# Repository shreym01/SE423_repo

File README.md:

# SE423Spring25
Lab assignment repository for SE423 Spring 2025

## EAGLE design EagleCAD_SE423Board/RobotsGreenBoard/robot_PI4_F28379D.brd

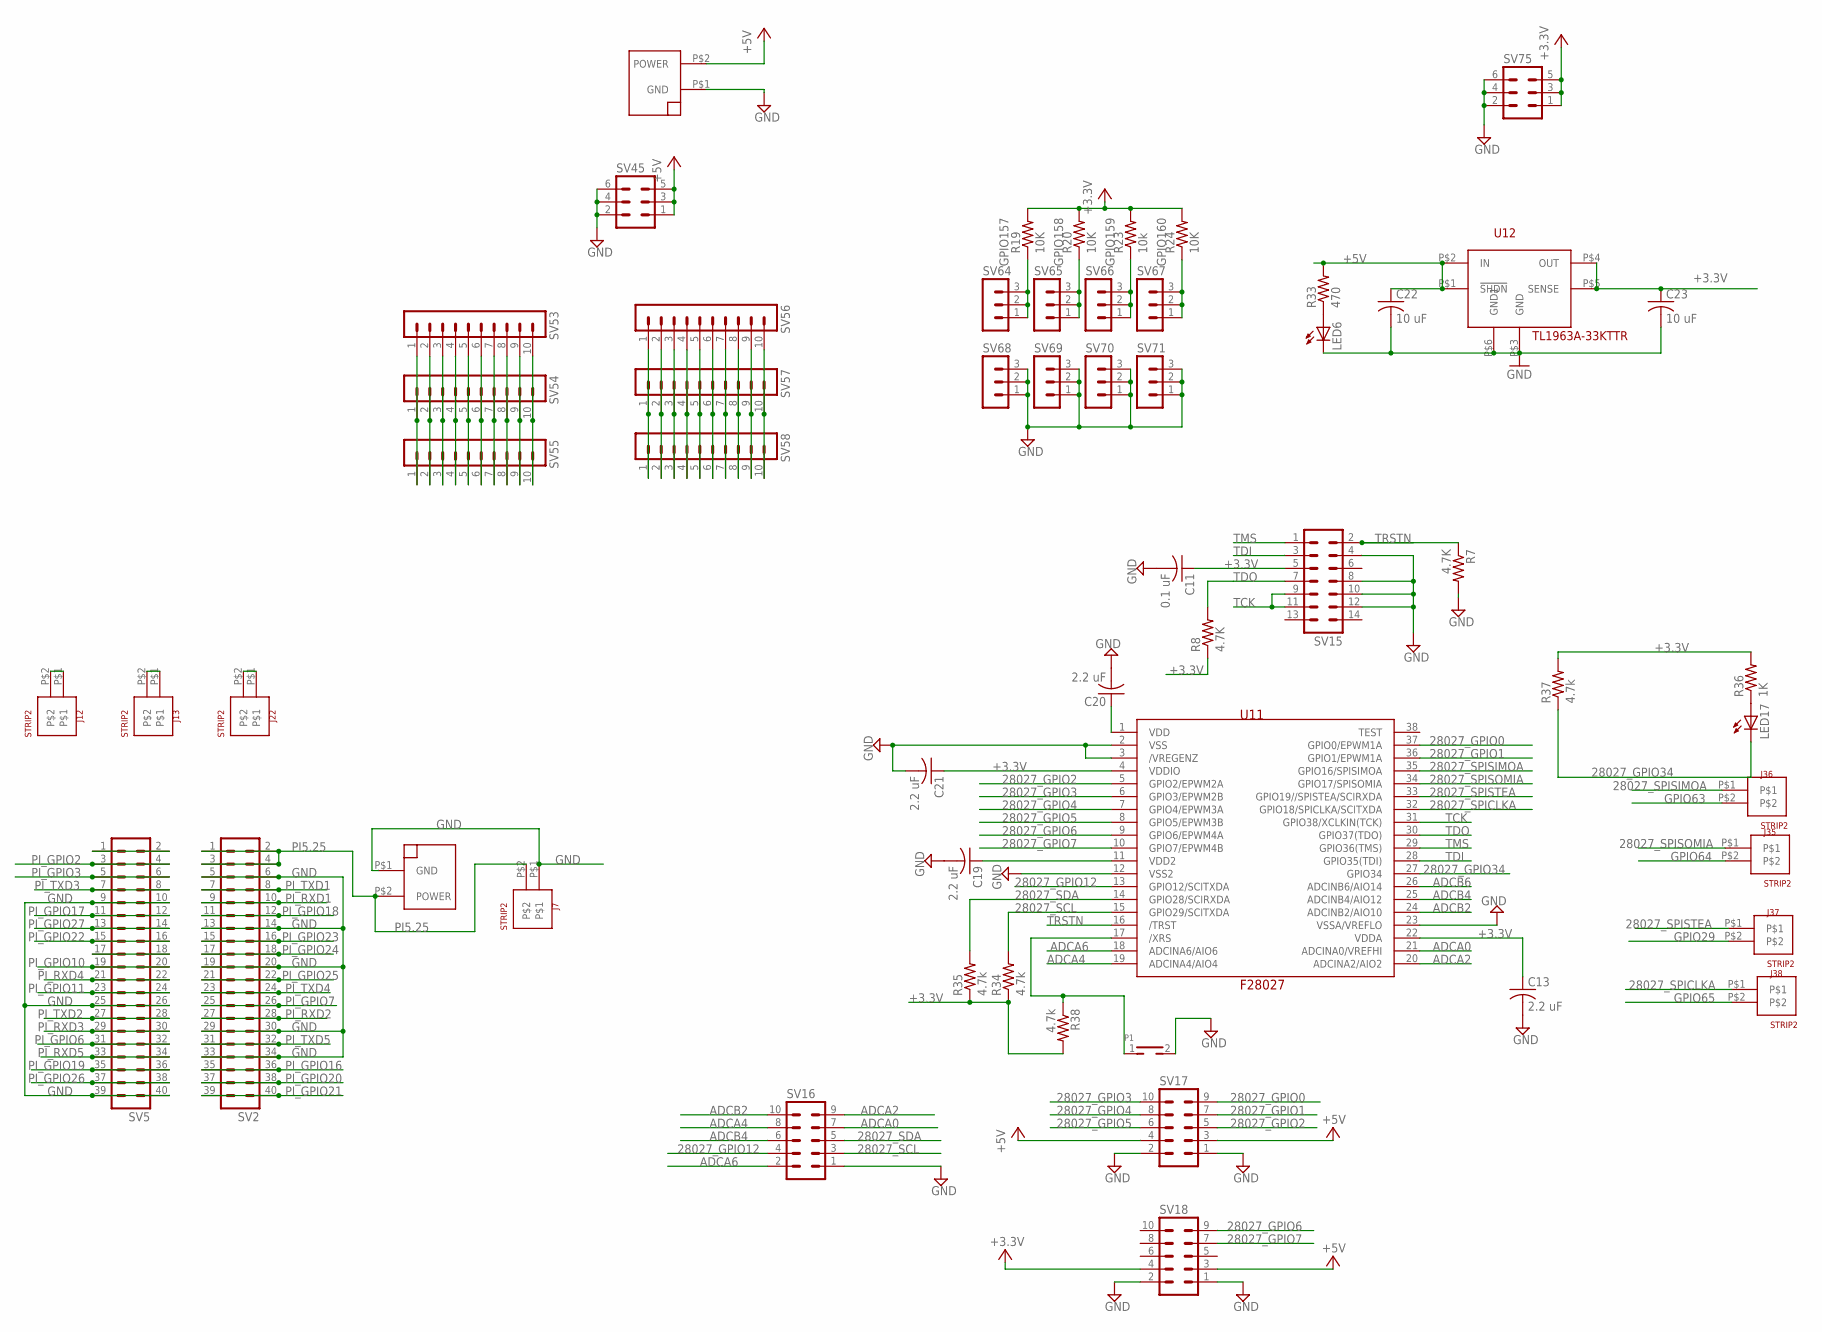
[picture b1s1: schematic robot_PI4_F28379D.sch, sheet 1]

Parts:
C11: 0.1 uF; C1206
C13, C19, C20, C21: 2.2 uF; C1206
C22, C23: 10 uF; C1206
J7, J12, J13, J22, J35, J36, J37, J38: STRIP2
LED6, LED17: LEDCHIPLED_1206; CHIPLED_1206
P1: TH_PUSHBOTTON; TH_PUSHBUTTON
P2, P3: MOLEX_POWER
R7, R8: 4.7K; M1206
R19, R20, R24: 10K; M1206
R23: 10k; M1206
R33: 470; M1206
R34, R35, R37, R38: 4.7k; M1206
R36: 1K; M1206
SV2, SV5: MA20-2
SV15: MA07-2
SV16, SV17, SV18: MA05-2
SV45, SV75: MA03-2
SV53, SV54, SV55, SV56, SV57, SV58: MA10-1
SV64, SV65, SV66, SV67, SV68, SV69, SV70, SV71: MA03-1
U11: F28027; DA38
U12: TL1963A-33KTTR; TL1963AKTTR

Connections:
28027_GPIO0: SV17.9, U11.37 (GPIO0/EPWM1A)
28027_GPIO1: SV17.7, U11.36 (GPIO1/EPWM1A)
28027_GPIO2: SV17.5, U11.5 (GPIO2/EPWM2A)
28027_GPIO3: SV17.10, U11.6 (GPIO3/EPWM2B)
28027_GPIO4: SV17.8, U11.7 (GPIO4/EPWM3A)
28027_GPIO5: SV17.6, U11.8 (GPIO5/EPWM3B)
28027_GPIO6: SV18.9, U11.9 (GPIO6/EPWM4A)
28027_GPIO7: SV18.7, U11.10 (GPIO7/EPWM4B)
28027_GPIO12: SV16.4, U11.13 (GPIO12/SCITXDA)
28027_GPIO34: LED17.C, R37.1, U11.27 (GPIO34)
28027_SCL: R34.2, SV16.3, U11.15 (GPIO29/SCITXDA)
28027_SDA: R35.2, SV16.5, U11.14 (GPIO28/SCIRXDA)
28027_SPICLKA: J38.P$1, U11.32 (GPIO18/SPICLKA/SCITXDA)
28027_SPISIMOA: J36.P$1, U11.35 (GPIO16/SPISIMOA)
28027_SPISOMIA: J35.P$1, U11.34 (GPIO17/SPISOMIA)
28027_SPISTEA: J37.P$1, U11.33 (GPIO19//SPISTEA/SCIRXDA)
+3.3V: C11.1, C13.1, C21.1, C23.1, R8.1, R19.2, R20.2, R23.2, R24.2, R34.1, R35.1, R36.2, R37.2, R38.2, SV15.5, SV18.4, SV75.1, SV75.3, SV75.5, U11.4 (VDDIO), U11.22 (VDDA), U12.P$4 (OUT), U12.P$5 (SENSE); also elsewhere on the board
+5V: C22.1, P3.P$2 (POWER), R33.2, SV17.3, SV17.4, SV18.3, SV45.1, SV45.3, SV45.5, U12.P$1 (!SHDN), U12.P$2 (IN); also elsewhere on the board
ADCA0: SV16.7, U11.21 (ADCINA0/VREFHI)
ADCA2: SV16.9, U11.20 (ADCINA2/AIO2)
ADCA4: SV16.8, U11.19 (ADCINA4/AIO4)
ADCA6: SV16.2, U11.18 (ADCINA6/AIO6)
ADCB2: SV16.10, U11.24 (ADCINB2/AIO10)
ADCB4: SV16.6, U11.25 (ADCINB4/AIO12)
ADCB6: U11.26 (ADCINB6/AIO14)
GND: C11.2, C13.2, C19.2, C20.2, C21.2, C22.2, C23.2, J7.P$1, LED6.C, P1.2, P2.P$1 (GND), P3.P$1 (GND), R7.2, SV2.5, SV2.6, SV2.13, SV2.14, SV2.19, SV2.20, SV2.29, SV2.30, SV2.33, SV2.34, SV5.9, SV5.10, SV5.25, SV5.26, SV5.39, SV5.40, SV15.4, SV15.8, SV15.10, SV15.12, SV16.1, SV17.1, SV17.2, SV18.1, SV18.2, SV45.2, SV45.4, SV45.6, SV68.1, SV68.2, SV68.3, SV69.1, SV69.2, SV69.3, SV70.1, SV70.2, SV70.3, SV71.1, SV71.2, SV71.3, SV75.2, SV75.4, SV75.6, U11.2 (VSS), U11.3 (/VREGENZ), U11.12 (VSS2), U11.23 (VSSA/VREFLO), U12.P$3 (GND), U12.P$6 (GND1); also elsewhere on the board
GPIO29: J37.P$2; also elsewhere on the board
GPIO63: J36.P$2; also elsewhere on the board
GPIO64: J35.P$2; also elsewhere on the board
GPIO65: J38.P$2; also elsewhere on the board
GPIO157: R19.1, SV64.1, SV64.2, SV64.3; also elsewhere on the board
GPIO158: R20.1, SV65.1, SV65.2, SV65.3; also elsewhere on the board
GPIO159: R23.1, SV66.1, SV66.2, SV66.3; also elsewhere on the board
GPIO160: R24.1, SV67.1, SV67.2, SV67.3; also elsewhere on the board
unnamed: SV5.1, SV5.2
unnamed: SV5.17, SV5.18
unnamed: LED6.A, R33.1
unnamed: J12.P$1, J12.P$2
unnamed: J13.P$1, J13.P$2
unnamed: J22.P$1, J22.P$2
unnamed: SV53.1, SV54.1, SV55.1
unnamed: SV53.2, SV54.2, SV55.2
unnamed: SV53.3, SV54.3, SV55.3
unnamed: SV53.4, SV54.4, SV55.4
unnamed: SV53.5, SV54.5, SV55.5
unnamed: SV53.6, SV54.6, SV55.6
unnamed: SV53.7, SV54.7, SV55.7
unnamed: SV53.8, SV54.8, SV55.8
unnamed: SV53.9, SV54.9, SV55.9
unnamed: SV53.10, SV54.10, SV55.10
unnamed: SV56.1, SV57.1, SV58.1
unnamed: SV56.2, SV57.2, SV58.2
unnamed: SV56.3, SV57.3, SV58.3
unnamed: SV56.4, SV57.4, SV58.4
unnamed: SV56.5, SV57.5, SV58.5
unnamed: SV56.6, SV57.6, SV58.6
unnamed: SV56.7, SV57.7, SV58.7
unnamed: SV56.8, SV57.8, SV58.8
unnamed: SV56.9, SV57.9, SV58.9
unnamed: SV56.10, SV57.10, SV58.10
unnamed: C20.1, U11.1 (VDD)
unnamed: C19.1, U11.11 (VDD2)
unnamed: P1.1, R38.1, U11.17 (/XRS)
unnamed: LED17.A, R36.1
PI5.25: J7.P$2, P2.P$2 (POWER), SV2.1, SV2.2, SV2.3, SV2.4
PI_GPIO2: SV5.3, SV5.4; also elsewhere on the board
PI_GPIO3: SV5.5, SV5.6; also elsewhere on the board
PI_GPIO6: SV5.31, SV5.32; also elsewhere on the board
PI_GPIO7: SV2.25, SV2.26; also elsewhere on the board
PI_GPIO10: SV5.19, SV5.20; also elsewhere on the board
PI_GPIO11: SV5.23, SV5.24; also elsewhere on the board
PI_GPIO16: SV2.35, SV2.36
PI_GPIO17: SV5.11, SV5.12
PI_GPIO18: SV2.11, SV2.12
PI_GPIO19: SV5.35, SV5.36
PI_GPIO20: SV2.37, SV2.38
PI_GPIO21: SV2.39, SV2.40
PI_GPIO22: SV5.15, SV5.16
PI_GPIO23: SV2.15, SV2.16
PI_GPIO24: SV2.17, SV2.18
PI_GPIO25: SV2.21, SV2.22
PI_GPIO26: SV5.37, SV5.38
PI_GPIO27: SV5.13, SV5.14
PI_RXD1: SV2.9, SV2.10; also elsewhere on the board
PI_RXD2: SV2.27, SV2.28; also elsewhere on the board
PI_RXD3: SV5.29, SV5.30; also elsewhere on the board
PI_RXD4: SV5.21, SV5.22; also elsewhere on the board
PI_RXD5: SV5.33, SV5.34; also elsewhere on the board
PI_TXD1: SV2.7, SV2.8; also elsewhere on the board
PI_TXD2: SV5.27, SV5.28; also elsewhere on the board
PI_TXD3: SV5.7, SV5.8; also elsewhere on the board
PI_TXD4: SV2.23, SV2.24; also elsewhere on the board
PI_TXD5: SV2.31, SV2.32; also elsewhere on the board
TCK: SV15.9, SV15.11, U11.31 (GPIO38/XCLKIN(TCK))
TDI: SV15.3, U11.28 (GPIO35(TDI))
TDO: R8.2, SV15.7, U11.30 (GPIO37(TDO))
TMS: SV15.1, U11.29 (GPIO36(TMS))
TRSTN: R7.1, SV15.2, U11.16 (/TRST)

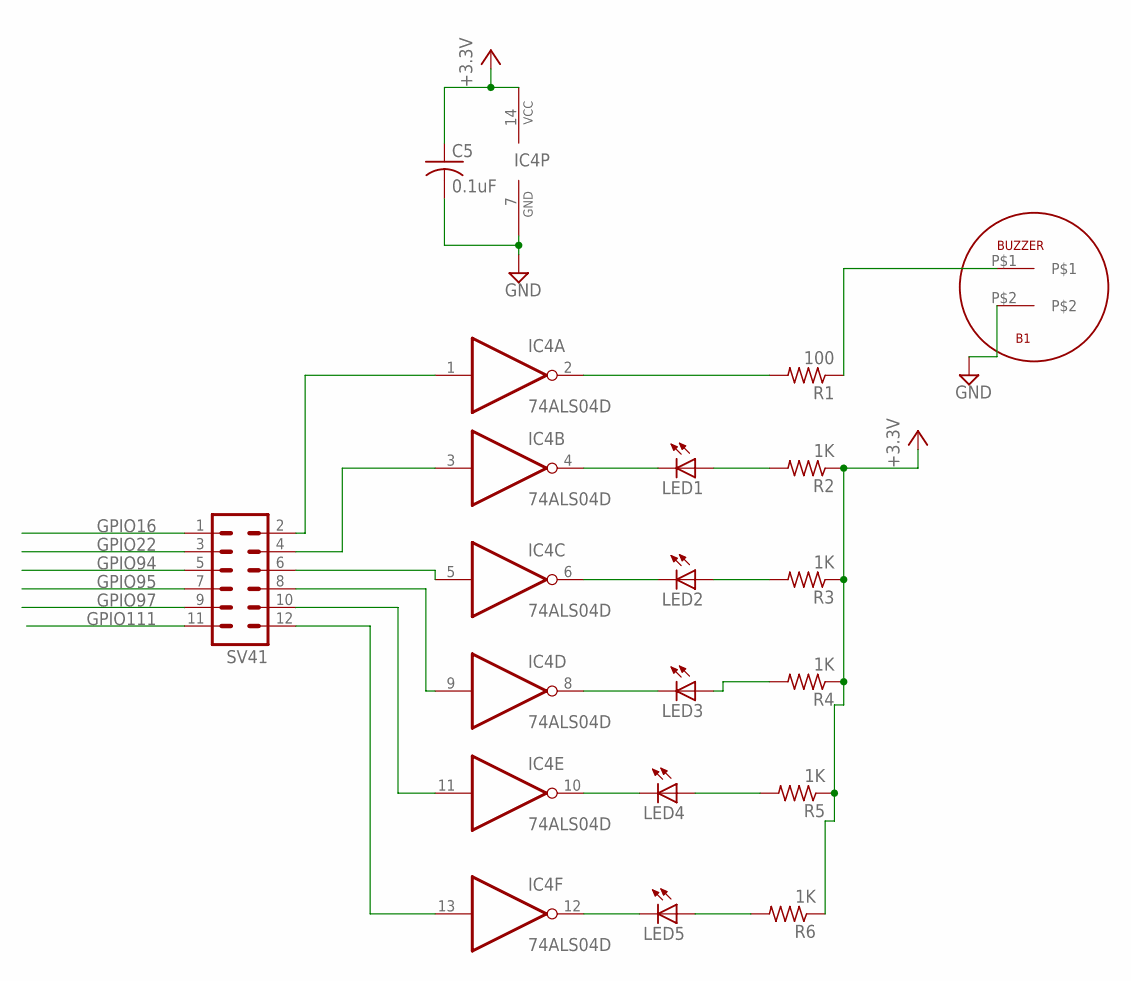
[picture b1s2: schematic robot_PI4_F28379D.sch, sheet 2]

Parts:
B1: BUZZER
C5: 0.1uF; C0805
IC4: 74ALS04D; SO14
LED1, LED2, LED3, LED4, LED5: LEDCHIPLED_1206; CHIPLED_1206
R1: 100; R1206
R2, R3, R4, R5, R6: 1K; R1206
SV41: MA06-2

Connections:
+3.3V: C5.1, IC4.14 (VCC), R2.1, R3.1, R4.1, R5.1, R6.1; also elsewhere on the board
GND: B1.P$2, C5.2, IC4.7 (GND); also elsewhere on the board
GPIO16: SV41.1; also elsewhere on the board
GPIO22: SV41.3; also elsewhere on the board
GPIO94: SV41.5; also elsewhere on the board
GPIO95: SV41.7; also elsewhere on the board
GPIO97: SV41.9; also elsewhere on the board
GPIO111: SV41.11; also elsewhere on the board
unnamed: IC4.2 (O), R1.2
unnamed: IC4.4 (O), LED1.C
unnamed: B1.P$1, R1.1
unnamed: LED1.A, R2.2
unnamed: LED2.A, R3.2
unnamed: LED3.A, R4.2
unnamed: LED4.A, R5.2
unnamed: LED5.A, R6.2
unnamed: IC4.12 (O), LED5.C
unnamed: IC4.10 (O), LED4.C
unnamed: IC4.8 (O), LED3.C
unnamed: IC4.6 (O), LED2.C
unnamed: IC4.1 (I), SV41.2
unnamed: IC4.3 (I), SV41.4
unnamed: IC4.5 (I), SV41.6
unnamed: IC4.9 (I), SV41.8
unnamed: IC4.11 (I), SV41.10
unnamed: IC4.13 (I), SV41.12

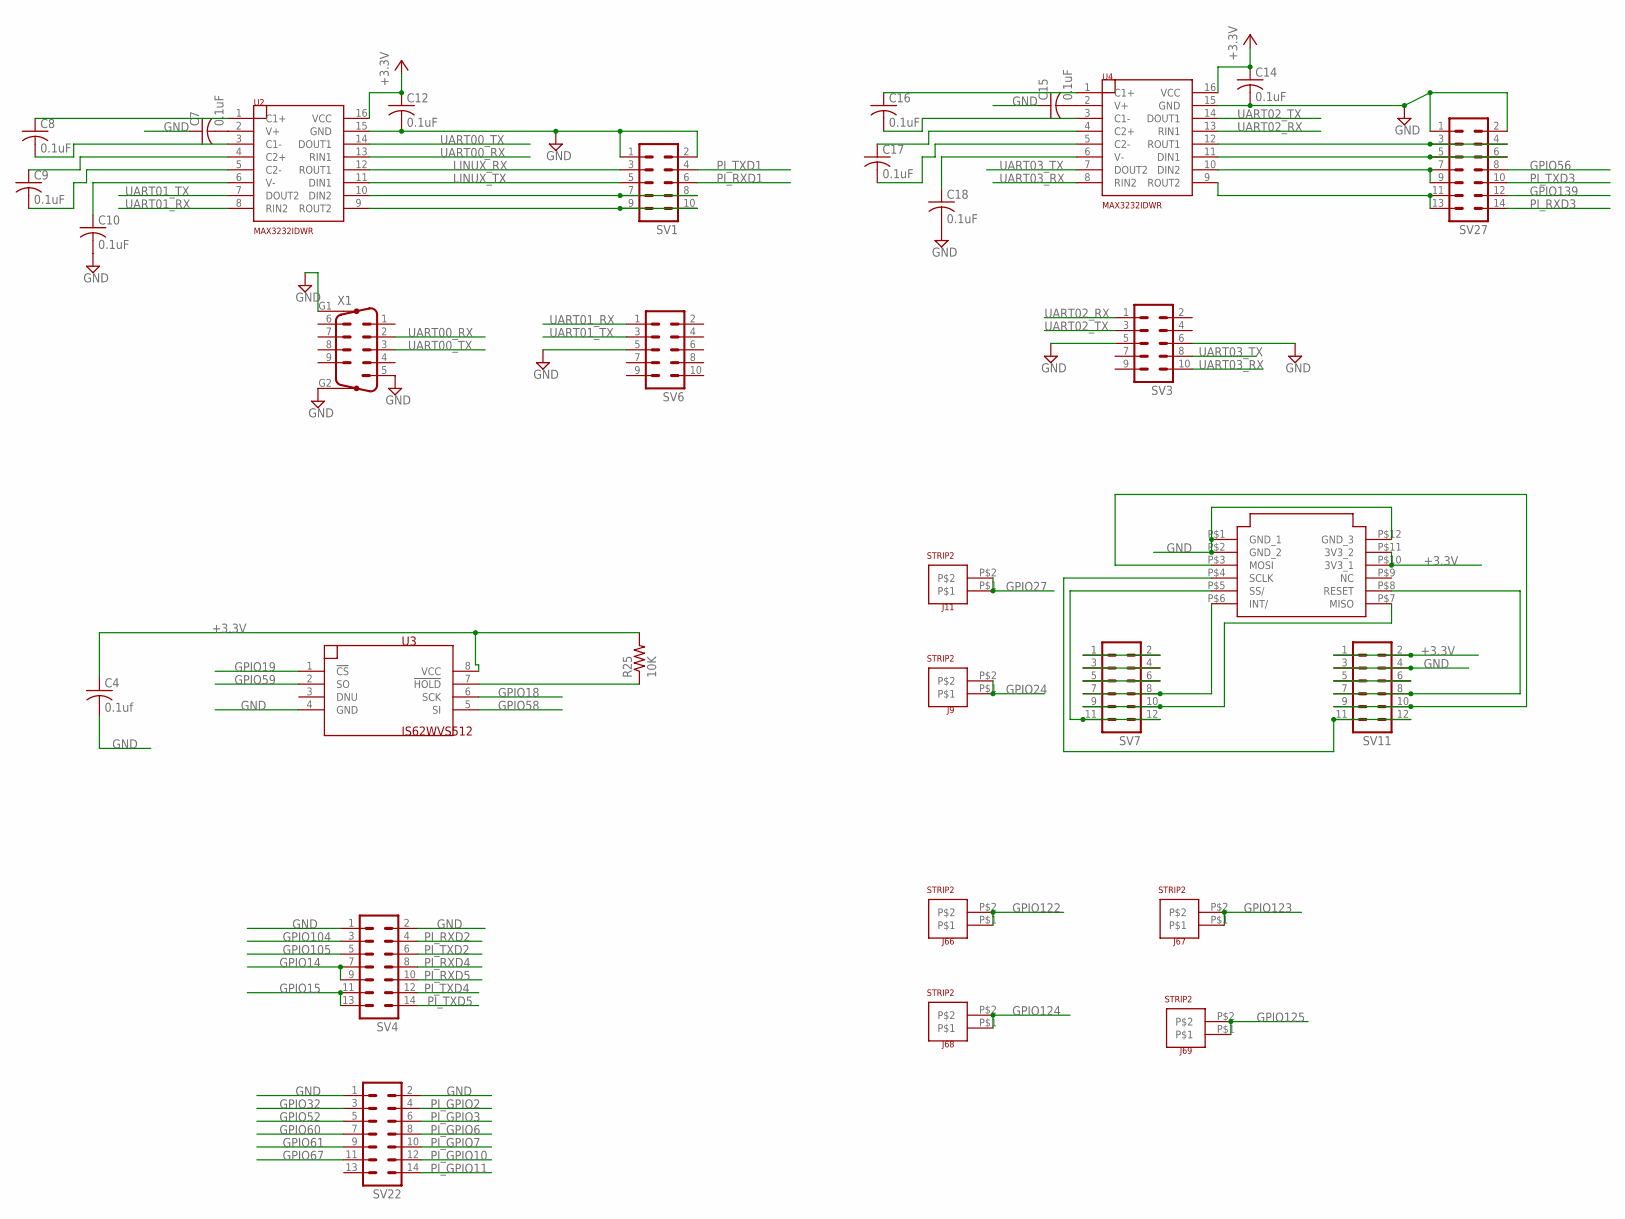
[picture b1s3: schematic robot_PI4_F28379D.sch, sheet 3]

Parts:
C4: 0.1uf; C1206
C7, C8, C9, C10, C12, C14, C15, C16, C17, C18: 0.1uF; C0805K
ETH1: USR_ES1_W5500
J9, J11, J66, J67, J68, J69: STRIP2
R25: 10K; M1206
SV1, SV3, SV6: MA05-2
SV4, SV22, SV27: MA07-2
SV7, SV11: MA06-2
U2, U4: MAX3232IDWR; SO16W
U3: IS62WVS512; SO08
X1: M09HP

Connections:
+3.3V: C4.1, C12.1, C14.1, ETH1.P$10 (3V3_1), ETH1.P$11 (3V3_2), R25.2, SV11.1, SV11.2, U2.16 (VCC), U3.8 (VCC), U4.16 (VCC); also elsewhere on the board
GND: C4.2, C7.1, C10.2, C12.2, C14.2, C15.1, C18.2, ETH1.P$1 (GND_1), ETH1.P$2 (GND_2), ETH1.P$12 (GND_3), SV1.1, SV1.2, SV3.5, SV3.6, SV4.1, SV4.2, SV6.5, SV11.3, SV11.4, SV22.1, SV22.2, SV27.1, SV27.2, U2.15 (GND), U3.4 (GND), U4.15 (GND), X1.5, X1.G1, X1.G2; also elsewhere on the board
GPIO14: SV4.7, SV4.9; also elsewhere on the board
GPIO15: SV4.11, SV4.13; also elsewhere on the board
GPIO18: U3.6 (SCK); also elsewhere on the board
GPIO19: U3.1 (!CS); also elsewhere on the board
GPIO24: J9.P$1, J9.P$2; also elsewhere on the board
GPIO27: J11.P$1, J11.P$2; also elsewhere on the board
GPIO32: SV22.3; also elsewhere on the board
GPIO52: SV22.5; also elsewhere on the board
GPIO56: SV27.8; also elsewhere on the board
GPIO58: U3.5 (SI); also elsewhere on the board
GPIO59: U3.2 (SO); also elsewhere on the board
GPIO60: SV22.7; also elsewhere on the board
GPIO61: SV22.9; also elsewhere on the board
GPIO67: SV22.11; also elsewhere on the board
GPIO104: SV4.3; also elsewhere on the board
GPIO105: SV4.5; also elsewhere on the board
GPIO122: J66.P$1, J66.P$2; also elsewhere on the board
GPIO123: J67.P$1, J67.P$2; also elsewhere on the board
GPIO124: J68.P$1, J68.P$2; also elsewhere on the board
GPIO125: J69.P$1, J69.P$2; also elsewhere on the board
GPIO139: SV27.12; also elsewhere on the board
LINUX_RX: SV1.3, U2.12 (ROUT1)
LINUX_TX: SV1.5, U2.11 (DIN1)
unnamed: SV1.7, SV1.8, U2.10 (DIN2)
unnamed: C7.2, U2.2 (V+)
unnamed: C16.1, U4.1 (C1+)
unnamed: C16.2, U4.3 (C1-)
unnamed: C17.1, U4.4 (C2+)
unnamed: C17.2, U4.5 (C2-)
unnamed: SV1.9, SV1.10, U2.9 (ROUT2)
unnamed: C18.1, U4.6 (V-)
unnamed: C15.2, U4.2 (V+)
unnamed: SV27.11, SV27.13, U4.9 (ROUT2)
unnamed: SV27.3, SV27.4, U4.12 (ROUT1)
unnamed: SV27.5, SV27.6, U4.11 (DIN1)
unnamed: SV27.7, SV27.9, U4.10 (DIN2)
unnamed: C8.1, U2.1 (C1+)
unnamed: C8.2, U2.3 (C1-)
unnamed: C9.1, U2.4 (C2+)
unnamed: C9.2, U2.5 (C2-)
unnamed: C10.1, U2.6 (V-)
unnamed: R25.1, U3.7 (!HOLD)
unnamed: SV7.1, SV7.2
unnamed: SV7.3, SV7.4
unnamed: SV7.5, SV7.6
unnamed: ETH1.P$6 (INT/), SV7.7, SV7.8
unnamed: ETH1.P$7 (MISO), SV7.9, SV7.10
unnamed: ETH1.P$5 (SS/), SV7.11, SV7.12
unnamed: SV11.5, SV11.6
unnamed: ETH1.P$8 (RESET), SV11.7, SV11.8
unnamed: ETH1.P$3 (MOSI), SV11.9, SV11.10
unnamed: ETH1.P$4 (SCLK), SV11.11, SV11.12
PI_GPIO2: SV22.4; also elsewhere on the board
PI_GPIO3: SV22.6; also elsewhere on the board
PI_GPIO6: SV22.8; also elsewhere on the board
PI_GPIO7: SV22.10; also elsewhere on the board
PI_GPIO10: SV22.12; also elsewhere on the board
PI_GPIO11: SV22.14; also elsewhere on the board
PI_RXD1: SV1.6; also elsewhere on the board
PI_RXD2: SV4.4; also elsewhere on the board
PI_RXD3: SV27.14; also elsewhere on the board
PI_RXD4: SV4.8; also elsewhere on the board
PI_RXD5: SV4.10; also elsewhere on the board
PI_TXD1: SV1.4; also elsewhere on the board
PI_TXD2: SV4.6; also elsewhere on the board
PI_TXD3: SV27.10; also elsewhere on the board
PI_TXD4: SV4.12; also elsewhere on the board
PI_TXD5: SV4.14; also elsewhere on the board
UART00_RX: U2.13 (RIN1), X1.2
UART00_TX: U2.14 (DOUT1), X1.3
UART01_RX: SV6.1, U2.8 (RIN2)
UART01_TX: SV6.3, U2.7 (DOUT2)
UART02_RX: SV3.1, U4.13 (RIN1)
UART02_TX: SV3.3, U4.14 (DOUT1)
UART03_RX: SV3.10, U4.8 (RIN2)
UART03_TX: SV3.8, U4.7 (DOUT2)

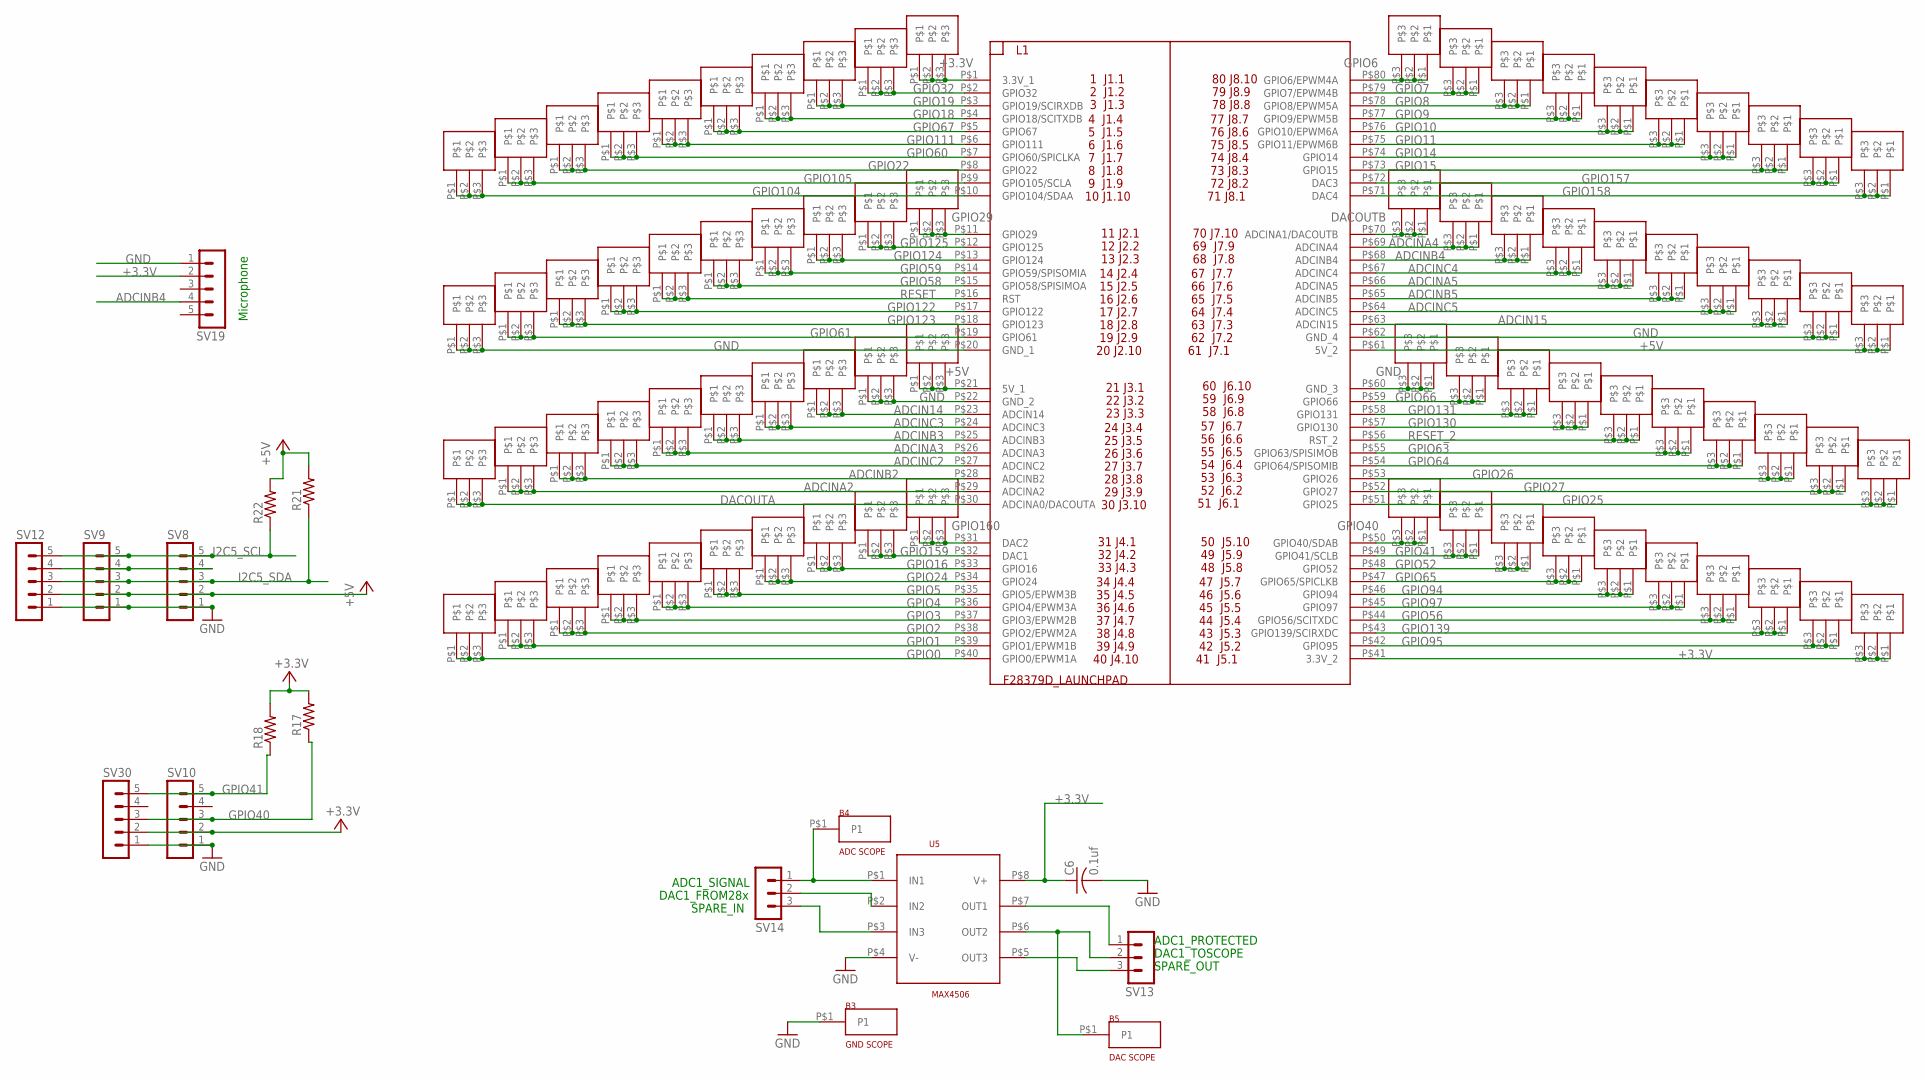
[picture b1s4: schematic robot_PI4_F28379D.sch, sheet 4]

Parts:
B3: GND SCOPE; BANANA_MALE
B4: ADC SCOPE; BANANA_MALE
B5: DAC SCOPE; BANANA_MALE
C6: 0.1uf; C1206
J10, J14, J15, J16, J17, J18, J19, J20, J21, J28, J29, J30, J31, J32, J33, J98, J99, J100, J101, J102, J103, J104, J105, J106, J107, J108, J109, J110, J111, J112, J113, J114, J115, J116, J117, J118, J119, J120, J121, J122, J133, J134, J135, J136, J137, J138, J139, J140, J141, J142, J143, J144, J145, J146, J147, J148, J149, J150, J151, J152, J153, J154, J155, J156, J157, J158, J159, J160, J161, J162, J163, J164, J165, J166, J167, J168, J169, J170, J176, J177: STRIP3
L1: F28379D_LAUNCHPAD
R17, R18, R21, R22: R-US_R1206; R1206
SV8, SV9, SV10, SV12, SV19, SV30: MA05-1
SV13, SV14: MA03-1
U5: MAX4506; SOIC-8

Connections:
+3.3V: C6.1, J10.P$1, J10.P$2, J10.P$3, J177.P$1, J177.P$2, J177.P$3, L1.P$1 (3.3V_1), L1.P$41 (3.3V_2), R17.2, R18.2, SV10.2, SV19.2, SV30.2, U5.P$8 (V+); also elsewhere on the board
+5V: J103.P$1, J103.P$2, J103.P$3, J152.P$1, J152.P$2, J152.P$3, L1.P$21 (5V_1), L1.P$61 (5V_2), R21.2, R22.2, SV8.2, SV9.2, SV12.2; also elsewhere on the board
ADCIN14: J105.P$1, J105.P$2, J105.P$3, L1.P$23 (ADCIN14)
ADCIN15: J150.P$1, J150.P$2, J150.P$3, L1.P$63 (ADCIN15)
ADCINA2: J111.P$1, J111.P$2, J111.P$3, L1.P$29 (ADCINA2)
ADCINA3: J108.P$1, J108.P$2, J108.P$3, L1.P$26 (ADCINA3)
ADCINA4: J144.P$1, J144.P$2, J144.P$3, L1.P$69 (ADCINA4)
ADCINA5: J147.P$1, J147.P$2, J147.P$3, L1.P$66 (ADCINA5)
ADCINB2: J110.P$1, J110.P$2, J110.P$3, L1.P$28 (ADCINB2)
ADCINB3: J107.P$1, J107.P$2, J107.P$3, L1.P$25 (ADCINB3)
ADCINB4: J145.P$1, J145.P$2, J145.P$3, L1.P$68 (ADCINB4), SV19.4
ADCINB5: J148.P$1, J148.P$2, J148.P$3, L1.P$65 (ADCINB5)
ADCINC2: J109.P$1, J109.P$2, J109.P$3, L1.P$27 (ADCINC2); also elsewhere on the board
ADCINC3: J106.P$1, J106.P$2, J106.P$3, L1.P$24 (ADCINC3); also elsewhere on the board
ADCINC4: J146.P$1, J146.P$2, J146.P$3, L1.P$67 (ADCINC4); also elsewhere on the board
ADCINC5: J149.P$1, J149.P$2, J149.P$3, L1.P$64 (ADCINC5); also elsewhere on the board
DACOUTA: J112.P$1, J112.P$2, J112.P$3, L1.P$30 (ADCINA0/DACOUTA)
DACOUTB: J143.P$1, J143.P$2, J143.P$3, L1.P$70 (ADCINA1/DACOUTB)
GND: B3.P$1, C6.2, J102.P$1, J102.P$2, J102.P$3, J104.P$1, J104.P$2, J104.P$3, J151.P$1, J151.P$2, J151.P$3, J153.P$1, J153.P$2, J153.P$3, L1.P$20 (GND_1), L1.P$22 (GND_2), L1.P$60 (GND_3), L1.P$62 (GND_4), SV8.1, SV9.1, SV10.1, SV12.1, SV19.1, SV30.1, U5.P$4 (V-); also elsewhere on the board
GPIO0: J122.P$1, J122.P$2, J122.P$3, L1.P$40 (GPIO0/EPWM1A); also elsewhere on the board
GPIO1: J121.P$1, J121.P$2, J121.P$3, L1.P$39 (GPIO1/EPWM1B); also elsewhere on the board
GPIO2: J120.P$1, J120.P$2, J120.P$3, L1.P$38 (GPIO2/EPWM2A); also elsewhere on the board
GPIO3: J119.P$1, J119.P$2, J119.P$3, L1.P$37 (GPIO3/EPWM2B); also elsewhere on the board
GPIO4: J118.P$1, J118.P$2, J118.P$3, L1.P$36 (GPIO4/EPWM3A); also elsewhere on the board
GPIO5: J117.P$1, J117.P$2, J117.P$3, L1.P$35 (GPIO5/EPWM3B); also elsewhere on the board
GPIO6: J133.P$1, J133.P$2, J133.P$3, L1.P$80 (GPIO6/EPWM4A); also elsewhere on the board
GPIO7: J134.P$1, J134.P$2, J134.P$3, L1.P$79 (GPIO7/EPWM4B); also elsewhere on the board
GPIO8: J135.P$1, J135.P$2, J135.P$3, L1.P$78 (GPIO8/EPWM5A); also elsewhere on the board
GPIO9: J136.P$1, J136.P$2, J136.P$3, L1.P$77 (GPIO9/EPWM5B); also elsewhere on the board
GPIO10: J137.P$1, J137.P$2, J137.P$3, L1.P$76 (GPIO10/EPWM6A); also elsewhere on the board
GPIO11: J138.P$1, J138.P$2, J138.P$3, L1.P$75 (GPIO11/EPWM6B)
GPIO14: J139.P$1, J139.P$2, J139.P$3, L1.P$74 (GPIO14); also elsewhere on the board
GPIO15: J140.P$1, J140.P$2, J140.P$3, L1.P$73 (GPIO15); also elsewhere on the board
GPIO16: J115.P$1, J115.P$2, J115.P$3, L1.P$33 (GPIO16); also elsewhere on the board
GPIO18: J16.P$1, J16.P$2, J16.P$3, L1.P$4 (GPIO18/SCITXDB); also elsewhere on the board
GPIO19: J15.P$1, J15.P$2, J15.P$3, L1.P$3 (GPIO19/SCIRXDB); also elsewhere on the board
GPIO22: J20.P$1, J20.P$2, J20.P$3, L1.P$8 (GPIO22); also elsewhere on the board
GPIO24: J116.P$1, J116.P$2, J116.P$3, L1.P$34 (GPIO24); also elsewhere on the board
GPIO25: J162.P$1, J162.P$2, J162.P$3, L1.P$51 (GPIO25); also elsewhere on the board
GPIO26: J160.P$1, J160.P$2, J160.P$3, L1.P$53 (GPIO26); also elsewhere on the board
GPIO27: J161.P$1, J161.P$2, J161.P$3, L1.P$52 (GPIO27); also elsewhere on the board
GPIO29: J29.P$1, J29.P$2, J29.P$3, L1.P$11 (GPIO29); also elsewhere on the board
GPIO32: J14.P$1, J14.P$2, J14.P$3, L1.P$2 (GPIO32); also elsewhere on the board
GPIO40: J163.P$1, J163.P$2, J163.P$3, L1.P$50 (GPIO40/SDAB), R17.1, SV10.3, SV30.3
GPIO41: J164.P$1, J164.P$2, J164.P$3, L1.P$49 (GPIO41/SCLB), R18.1, SV10.5, SV30.5
GPIO52: J165.P$1, J165.P$2, J165.P$3, L1.P$48 (GPIO52); also elsewhere on the board
GPIO56: J169.P$1, J169.P$2, J169.P$3, L1.P$44 (GPIO56/SCITXDC); also elsewhere on the board
GPIO58: J33.P$1, J33.P$2, J33.P$3, L1.P$15 (GPIO58/SPISIMOA); also elsewhere on the board
GPIO59: J32.P$1, J32.P$2, J32.P$3, L1.P$14 (GPIO59/SPISOMIA); also elsewhere on the board
GPIO60: J19.P$1, J19.P$2, J19.P$3, L1.P$7 (GPIO60/SPICLKA); also elsewhere on the board
GPIO61: J101.P$1, J101.P$2, J101.P$3, L1.P$19 (GPIO61); also elsewhere on the board
GPIO63: J158.P$1, J158.P$2, J158.P$3, L1.P$55 (GPIO63/SPISIMOB); also elsewhere on the board
GPIO64: J159.P$1, J159.P$2, J159.P$3, L1.P$54 (GPIO64/SPISOMIB); also elsewhere on the board
GPIO65: J166.P$1, J166.P$2, J166.P$3, L1.P$47 (GPIO65/SPICLKB); also elsewhere on the board
GPIO66: J154.P$1, J154.P$2, J154.P$3, L1.P$59 (GPIO66); also elsewhere on the board
GPIO67: J17.P$1, J17.P$2, J17.P$3, L1.P$5 (GPIO67); also elsewhere on the board
GPIO94: J167.P$1, J167.P$2, J167.P$3, L1.P$46 (GPIO94); also elsewhere on the board
GPIO95: J176.P$1, J176.P$2, J176.P$3, L1.P$42 (GPIO95); also elsewhere on the board
GPIO97: J168.P$1, J168.P$2, J168.P$3, L1.P$45 (GPIO97); also elsewhere on the board
GPIO104: J28.P$1, J28.P$2, J28.P$3, L1.P$10 (GPIO104/SDAA); also elsewhere on the board
GPIO105: J21.P$1, J21.P$2, J21.P$3, L1.P$9 (GPIO105/SCLA); also elsewhere on the board
GPIO111: J18.P$1, J18.P$2, J18.P$3, L1.P$6 (GPIO111); also elsewhere on the board
GPIO122: J99.P$1, J99.P$2, J99.P$3, L1.P$17 (GPIO122); also elsewhere on the board
GPIO123: J100.P$1, J100.P$2, J100.P$3, L1.P$18 (GPIO123); also elsewhere on the board
GPIO124: J31.P$1, J31.P$2, J31.P$3, L1.P$13 (GPIO124); also elsewhere on the board
GPIO125: J30.P$1, J30.P$2, J30.P$3, L1.P$12 (GPIO125); also elsewhere on the board
GPIO130: J156.P$1, J156.P$2, J156.P$3, L1.P$57 (GPIO130); also elsewhere on the board
GPIO131: J155.P$1, J155.P$2, J155.P$3, L1.P$58 (GPIO131); also elsewhere on the board
GPIO139: J170.P$1, J170.P$2, J170.P$3, L1.P$43 (GPIO139/SCIRXDC); also elsewhere on the board
GPIO157: J141.P$1, J141.P$2, J141.P$3, L1.P$72 (DAC3); also elsewhere on the board
GPIO158: J142.P$1, J142.P$2, J142.P$3, L1.P$71 (DAC4); also elsewhere on the board
GPIO159: J114.P$1, J114.P$2, J114.P$3, L1.P$32 (DAC1); also elsewhere on the board
GPIO160: J113.P$1, J113.P$2, J113.P$3, L1.P$31 (DAC2); also elsewhere on the board
I2C5_SCL: R22.1, SV8.5, SV9.5, SV12.5
I2C5_SDA: R21.1, SV8.3, SV9.3, SV12.3
unnamed: SV8.4, SV9.4, SV12.4
unnamed: SV13.1, U5.P$7 (OUT1)
unnamed: B5.P$1, SV13.2, U5.P$6 (OUT2)
unnamed: SV13.3, U5.P$5 (OUT3)
unnamed: B4.P$1, SV14.1, U5.P$1 (IN1)
unnamed: SV14.2, U5.P$2 (IN2)
unnamed: SV14.3, U5.P$3 (IN3)
RESET: J98.P$1, J98.P$2, J98.P$3, L1.P$16 (RST)
RESET_2: J157.P$1, J157.P$2, J157.P$3, L1.P$56 (RST_2)

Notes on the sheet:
ADC1_SIGNAL
ADC1_PROTECTED
DAC1_FROM28x
DAC1_TOSCOPE
SPARE_IN
SPARE_OUT
Microphone

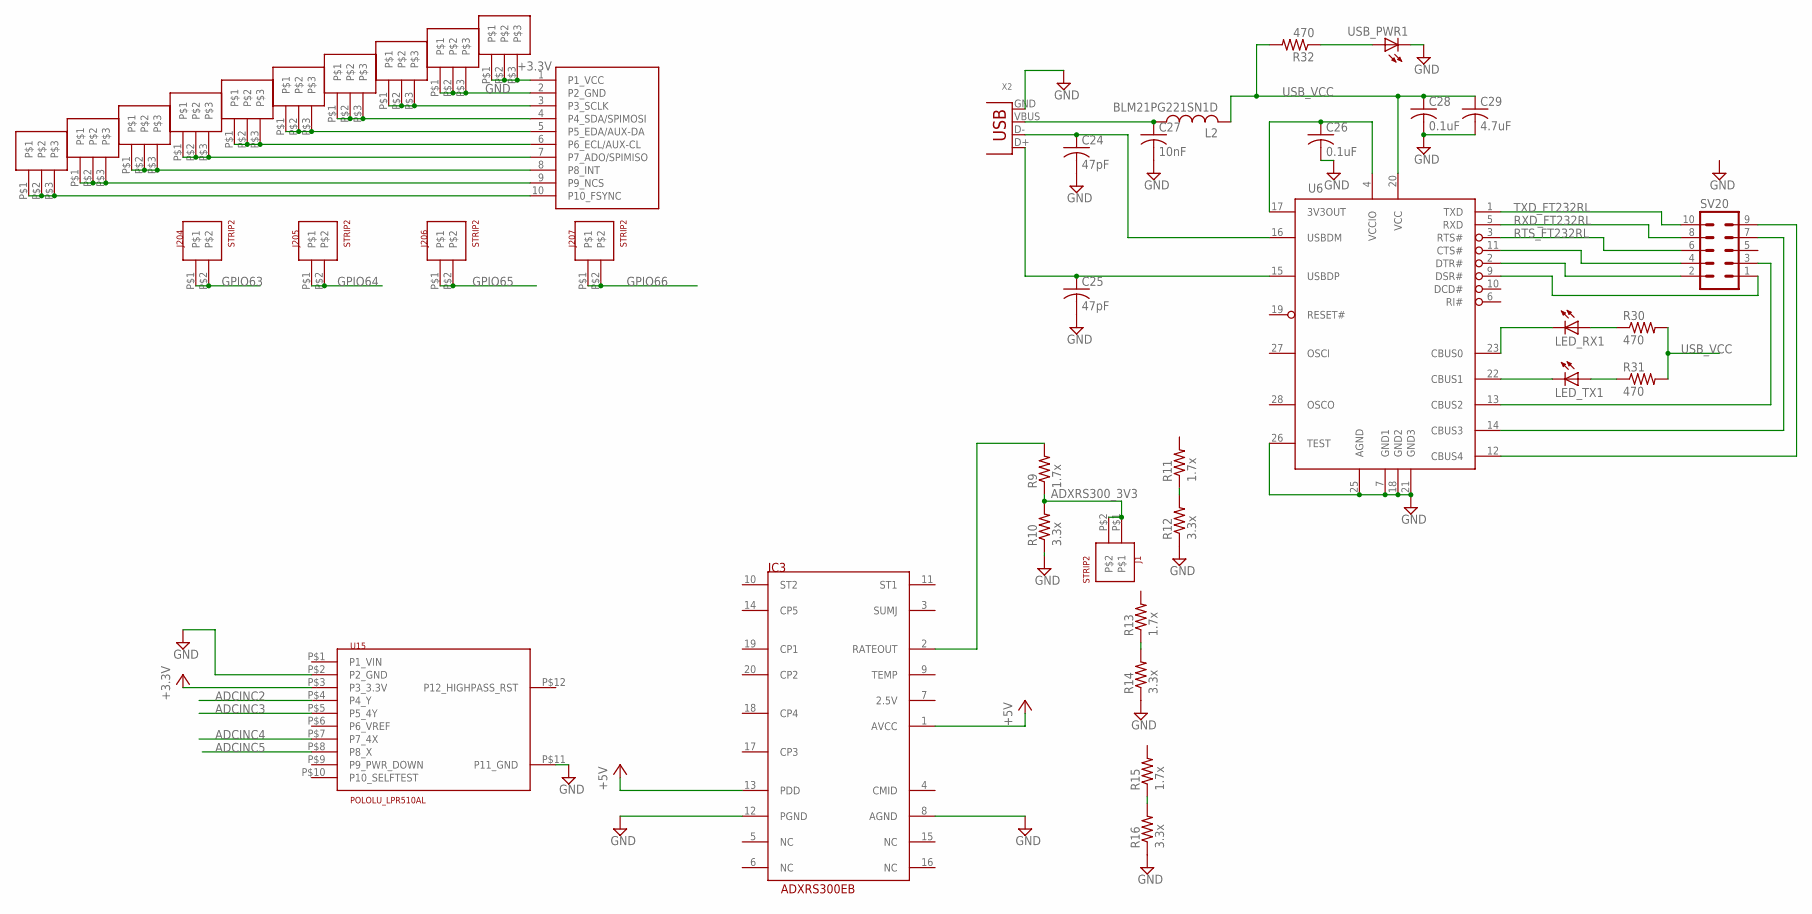
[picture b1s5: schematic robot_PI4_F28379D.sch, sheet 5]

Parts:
C24, C25: 47pF; C1206
C26, C28: 0.1uF; C1206
C27: 10nF; C1206
C29: 4.7uF; C1206
IC3: ADXRS300EB; DIL20
J1, J204, J205, J206, J207: STRIP2
J123, J124, J125, J126, J127, J128, J129, J130, J131, J132: STRIP3
L2: BLM21PG221SN1D; L0805
LED_RX1: LED3MM
LED_TX1: LED3MM
R9, R11, R13, R15: 1.7x; M1206
R10, R12, R14, R16: 3.3x; M1206
R30, R31, R32: 470; M1206
SV20: MA05-2
U6: FT232RL; SSOP28DB
U15: POLOLU_LPR510AL
U$1: MPU-9250-BB
USB_PWR1: LED3MM
X2: USB-B-H

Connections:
+3.3V: J123.P$1, J123.P$2, J123.P$3, U15.P$3 (P3_3.3V), U$1.1 (P1_VCC); also elsewhere on the board
+5V: IC3.1 (AVCC), IC3.13 (PDD); also elsewhere on the board
ADCINC2: U15.P$4 (P4_Y); also elsewhere on the board
ADCINC3: U15.P$5 (P5_4Y); also elsewhere on the board
ADCINC4: U15.P$7 (P7_4X); also elsewhere on the board
ADCINC5: U15.P$8 (P8_X); also elsewhere on the board
ADXRS300_3V3: J1.P$1, J1.P$2, R9.1, R10.2
GND: C24.2, C25.2, C26.2, C27.2, C28.2, C29.2, IC3.8 (AGND), IC3.12 (PGND), J124.P$1, J124.P$2, J124.P$3, R10.1, R12.1, R14.1, R16.1, U6.7 (GND1), U6.18 (GND2), U6.21 (GND3), U6.25 (AGND), U6.26 (TEST), U15.P$2 (P2_GND), U15.P$11 (P11_GND), U$1.2 (P2_GND), USB_PWR1.K (C), X2.GND; also elsewhere on the board
GPIO63: J204.P$1, J204.P$2; also elsewhere on the board
GPIO64: J205.P$1, J205.P$2; also elsewhere on the board
GPIO65: J206.P$1, J206.P$2; also elsewhere on the board
GPIO66: J207.P$1, J207.P$2; also elsewhere on the board
unnamed: C27.1, L2.1, X2.VBUS
unnamed: C24.1, U6.16 (USBDM), X2.D-
unnamed: C25.1, U6.15 (USBDP), X2.D+
unnamed: C26.1, U6.4 (VCCIO), U6.17 (3V3OUT)
unnamed: LED_TX1.K (C), U6.22 (CBUS1)
unnamed: LED_RX1.K (C), U6.23 (CBUS0)
unnamed: LED_RX1.A, R30.1
unnamed: LED_TX1.A, R31.1
unnamed: SV20.4, U6.11 (CTS#)
unnamed: SV20.2, U6.2 (DTR#)
unnamed: SV20.1, U6.9 (DSR#)
unnamed: R11.1, R12.2
unnamed: R13.1, R14.2
unnamed: SV20.3, U6.13 (CBUS2)
unnamed: SV20.7, U6.14 (CBUS3)
unnamed: SV20.9, U6.12 (CBUS4)
unnamed: R32.1, USB_PWR1.A
unnamed: R15.1, R16.2
unnamed: IC3.2 (RATEOUT), R9.2
unnamed: J125.P$1, J125.P$2, J125.P$3, U$1.3 (P3_SCLK)
unnamed: J126.P$1, J126.P$2, J126.P$3, U$1.4 (P4_SDA/SPIMOSI)
unnamed: J127.P$1, J127.P$2, J127.P$3, U$1.5 (P5_EDA/AUX-DA)
unnamed: J128.P$1, J128.P$2, J128.P$3, U$1.6 (P6_ECL/AUX-CL)
unnamed: J129.P$1, J129.P$2, J129.P$3, U$1.7 (P7_ADO/SPIMISO)
unnamed: J130.P$1, J130.P$2, J130.P$3, U$1.8 (P8_INT)
unnamed: J131.P$1, J131.P$2, J131.P$3, U$1.9 (P9_NCS)
unnamed: J132.P$1, J132.P$2, J132.P$3, U$1.10 (P10_FSYNC)
RTS_FT232RL: SV20.6, U6.3 (RTS#)
RXD_FT232RL: SV20.8, U6.5 (RXD)
TXD_FT232RL: SV20.10, U6.1 (TXD)
USB_VCC: C28.1, C29.1, L2.2, R30.2, R31.2, R32.2, U6.20 (VCC)
